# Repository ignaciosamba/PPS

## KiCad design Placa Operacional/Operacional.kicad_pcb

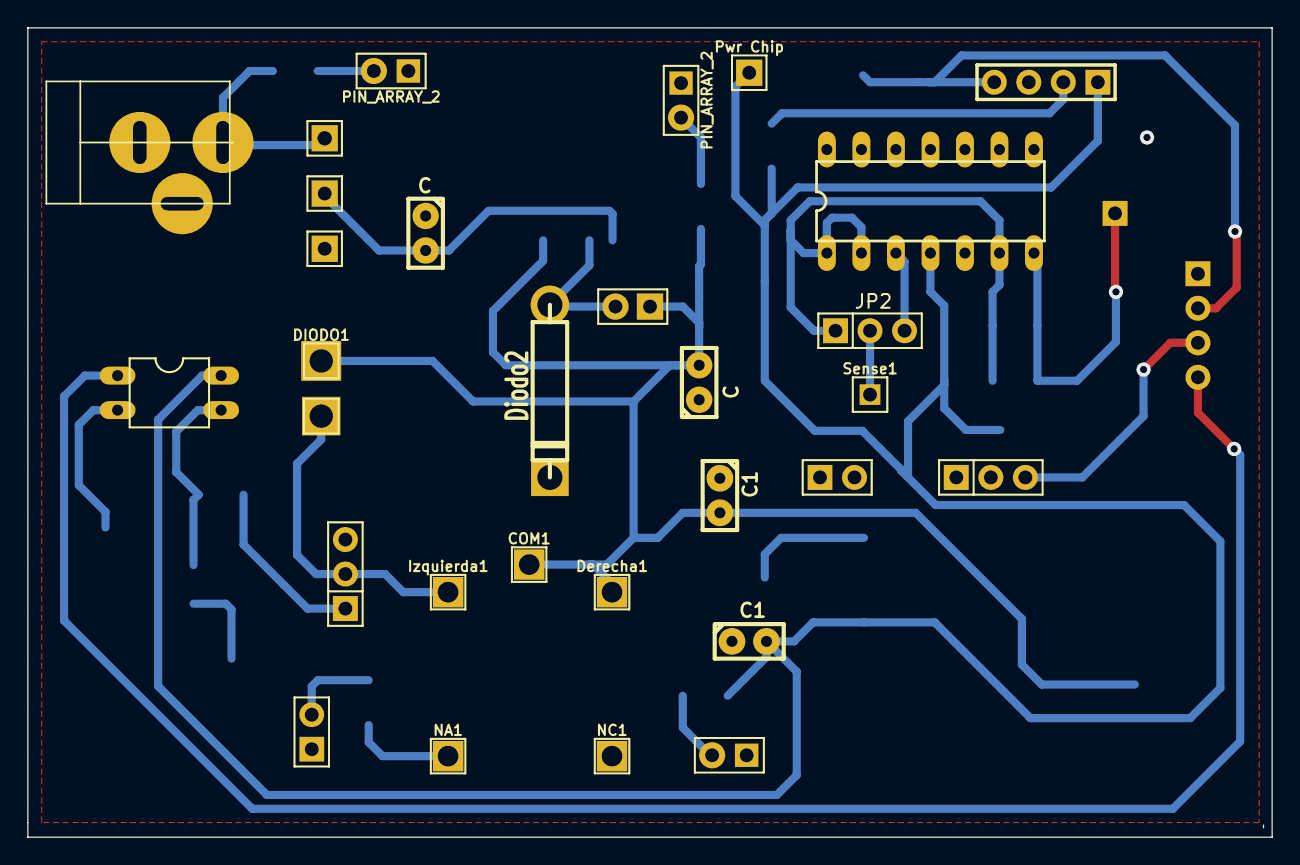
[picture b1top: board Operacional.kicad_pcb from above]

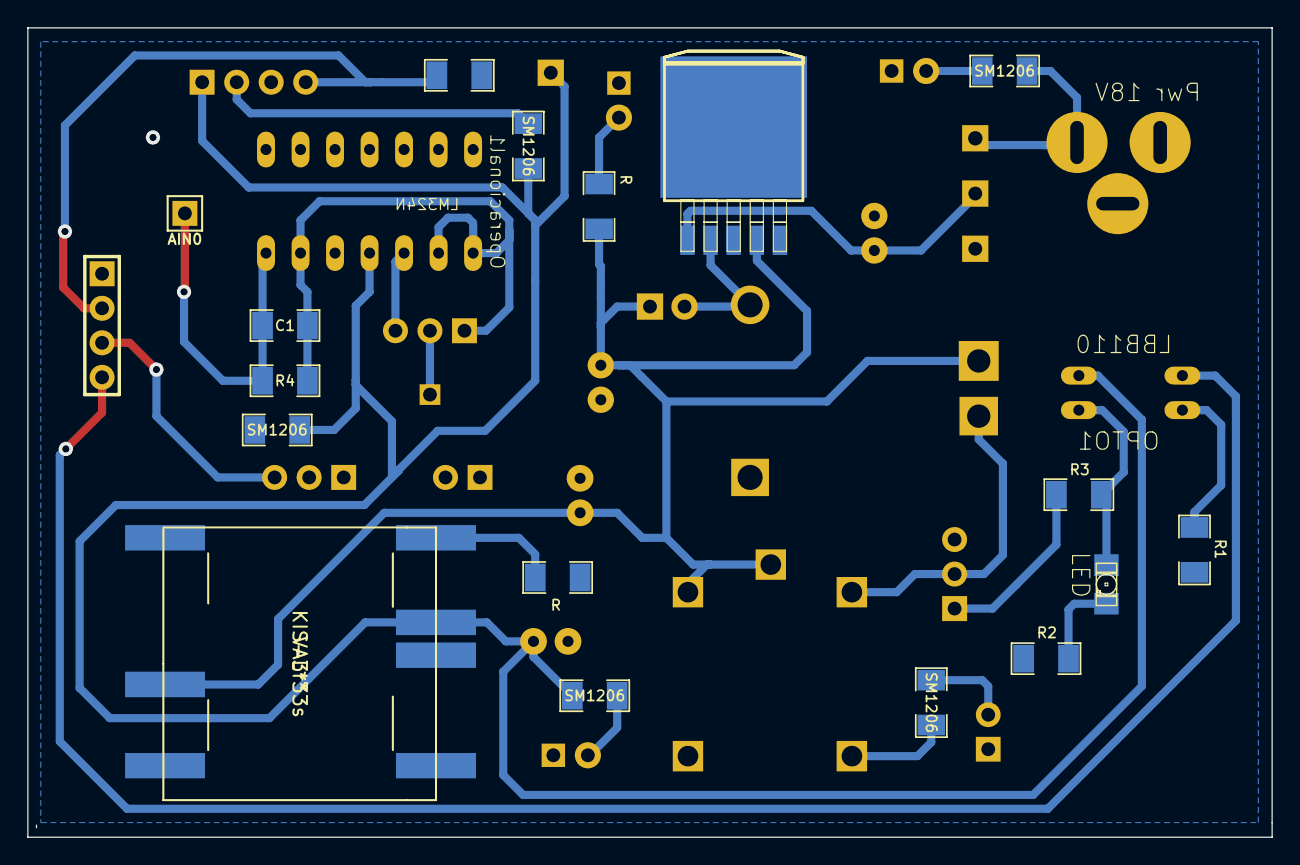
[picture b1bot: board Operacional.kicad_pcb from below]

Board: 2 copper layers, 91.6 x 59.6 mm, 32 parts (14 on the bottom side), 10 nets.

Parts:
AIN0: PIN_ARRAY_1
C: 100uF; C1
C1: 0.1uF; SM1206
C1#2, C1#3: C1
C#2: 1000uF; C1
COM1: PIN_ARRAY_1
DIODO1: PIN_ARRAY_1
Derecha1: PIN_ARRAY_1
Diodo2: D5
Izquierda1: PIN_ARRAY_1
JP2: PIN_ARRAY_3X1
KIS-3r33s: VAL**; KIS-3r33s
NA1: PIN_ARRAY_1
NC1: PIN_ARRAY_1
OPTO1: LBB110; optocoupler-2-DIL04
Operacional1: LM324N; op-amp-DIL14
PIN_ARRAY_2, PIN_ARRAY_2#2: Val**; PIN_ARRAY_2X1
Pwr Chip: PIN_ARRAY_1
R: 10K; SM1206
R1: 50; SM1206
R2: 1k; SM1206
R3, R4: 10k; SM1206
R#2: 1K; SM1206
SM1206, SM1206#2, SM1206#3, SM1206#4, SM1206#5: Val**; SM1206
Sense1: PIN_ARRAY_1

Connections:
GND: C.1, C1#2.1, C1#3.1, C#2.1, Diodo2.2, KIS-3r33s.2, KIS-3r33s.8, Operacional1.5, Operacional1.11, PIN_ARRAY_2.1, PIN_ARRAY_2#2.1, R.2, R1.2, R2.2, SM1206#5.2
unnamed: AIN0.1, C1.2, Operacional1.7, R4.2
unnamed: NA1.1, SM1206#3.1, SM1206#3.2
unnamed: C1.1, JP2.1, Operacional1.1, Operacional1.2, Operacional1.6, R4.1
unnamed: JP2.2, KIS-3r33s.5, R.1, Sense1.1
unnamed: JP2.3, Operacional1.3
unnamed: C.2, C1#2.2, C#2.2, COM1.1, DIODO1.1, Derecha1.1, Diodo2.1, KIS-3r33s.9, PIN_ARRAY_2.2, PIN_ARRAY_2#2.2, R#2.1, R#2.2, SM1206#2.1, SM1206#2.2
unnamed: OPTO1.2, R1.1
unnamed: OPTO1.3, R3.1
unnamed: C1#3.2, KIS-3r33s.4, OPTO1.4, Operacional1.4, Pwr Chip.1, SM1206.1, SM1206.2, SM1206#4.1, SM1206#4.2, SM1206#5.1

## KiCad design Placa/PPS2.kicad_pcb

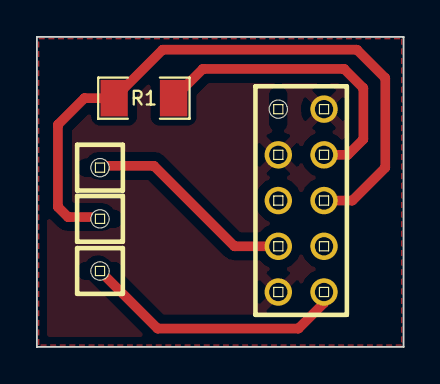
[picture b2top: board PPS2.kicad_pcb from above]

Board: 2 copper layers, 20.4 x 17.2 mm, 5 parts (0 on the bottom side), 5 nets.

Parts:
C2CLK1, C2DATOS1: PINHD-1X1; pinhead-1X01
JP1: PINHD-2X5; pinhead-2X05
PIN1: PINHD-1X1; pinhead-1X01
R1: 1K; SM1206

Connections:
GNDPWR: JP1.2, JP1.3, JP1.9
unnamed: JP1.4, R1.2
unnamed: C2CLK1.1, JP1.7
unnamed: C2DATOS1.1, JP1.6, R1.1
unnamed: JP1.10, PIN1.1

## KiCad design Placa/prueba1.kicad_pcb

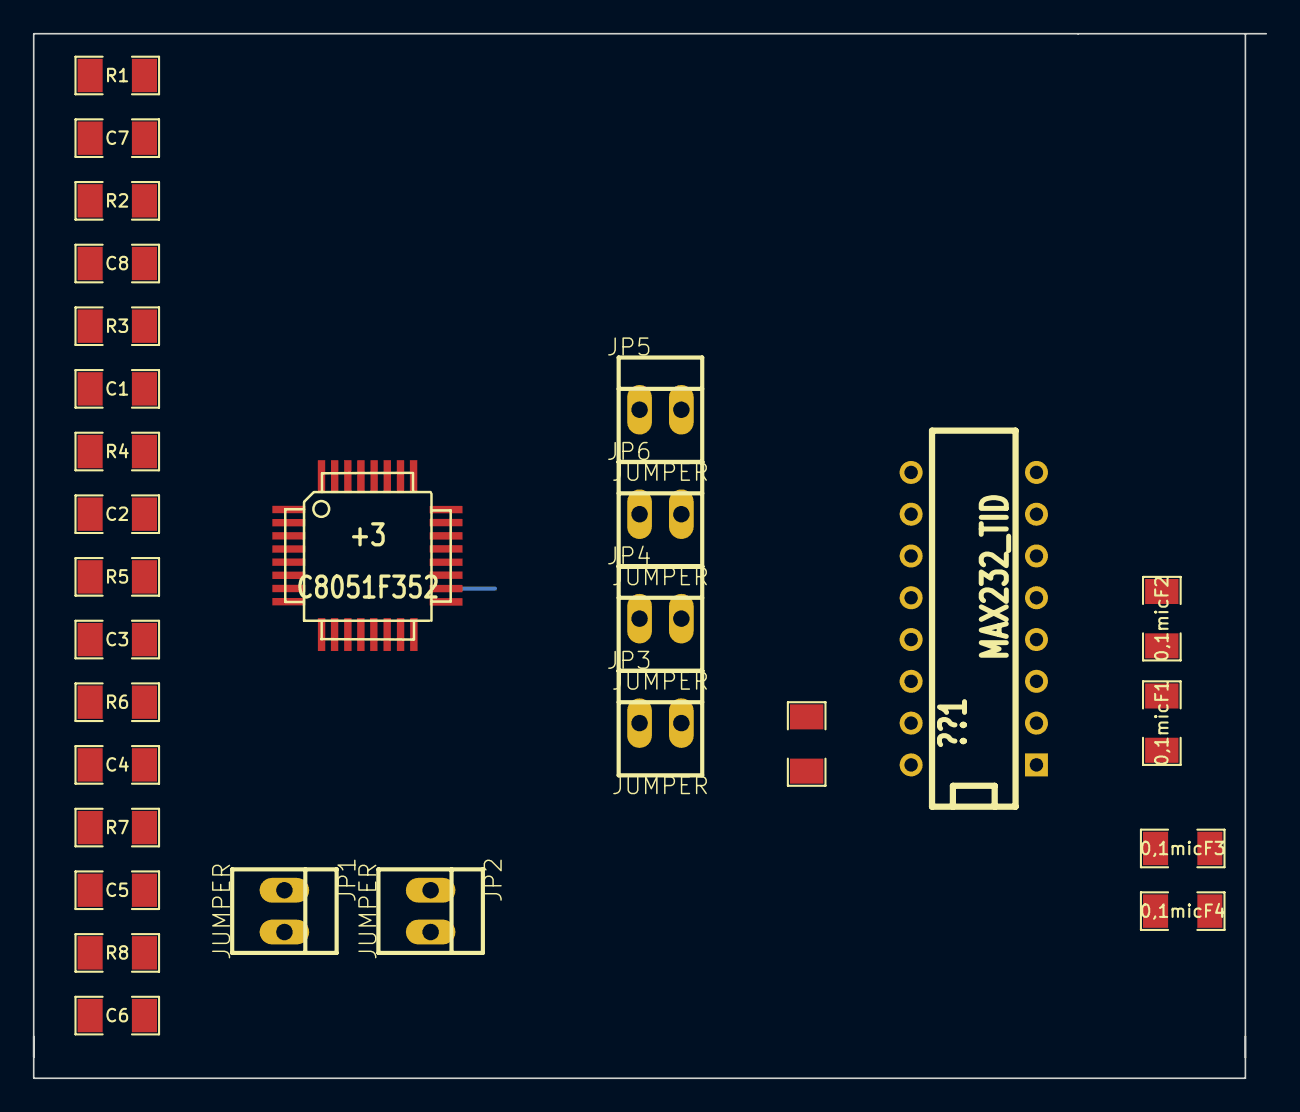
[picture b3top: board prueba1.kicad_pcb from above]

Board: 2 copper layers, 74.9 x 63.5 mm, 29 parts (0 on the bottom side), 36 nets.

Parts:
0,1micF1: C8; SM1206
0,1micF2: C9; SM1206
0,1micF3: C12; SM1206
0,1micF4: C10; SM1206
0,1micF5: C11; SM1206
+3: C8051F352; TQFP32
??1: MAX232_TID; DIP-16__300
C1, C2, C3, C4, C5, C6, C7, C8: 0,1micF; SM1206
JP1, JP2, JP3, JP4, JP5, JP6: JUMPER; PINHEAD1-2
R1, R2, R3, R4, R5, R6, R7, R8: 100ohm; SM1206

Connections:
DGND: C7.2, C8.2
GND: 0,1micF3.2, 0,1micF4.2, 0,1micF5.2, ??1.15
unnamed: 0,1micF1.1, ??1.1
unnamed: 0,1micF1.2, ??1.3
unnamed: +3.18, JP4.1
unnamed: +3.17, JP3.1
unnamed: +3.27, JP6.1
unnamed: +3.12, JP2.1
unnamed: +3.11, JP1.1
unnamed: 0,1micF2.1, ??1.4
unnamed: 0,1micF2.2, ??1.5
unnamed: +3.6, R6.2
unnamed: +3.1, R1.2
unnamed: +3.2, R2.2
unnamed: +3.3, R3.2
unnamed: +3.4, R4.2
unnamed: +3.5, R5.2
unnamed: 0,1micF5.1, ??1.16
unnamed: +3.7, R7.2
unnamed: +3.28, JP5.1
unnamed: ??1.9, JP6.2
unnamed: ??1.10, JP5.2
unnamed: ??1.12, JP4.2
unnamed: ??1.11, JP3.2
unnamed: 0,1micF3.1, ??1.6
unnamed: 0,1micF4.1, ??1.2
unnamed: +3.8, R8.2
unnamed: C8.1, R2.1
unnamed: C7.1, R1.1
unnamed: C1.1, R3.1
unnamed: C2.1, R4.1
unnamed: C3.1, R5.1
unnamed: C4.1, R6.1
unnamed: C5.1, R7.1
unnamed: C6.1, R8.1
VDD: +3.10, +3.21

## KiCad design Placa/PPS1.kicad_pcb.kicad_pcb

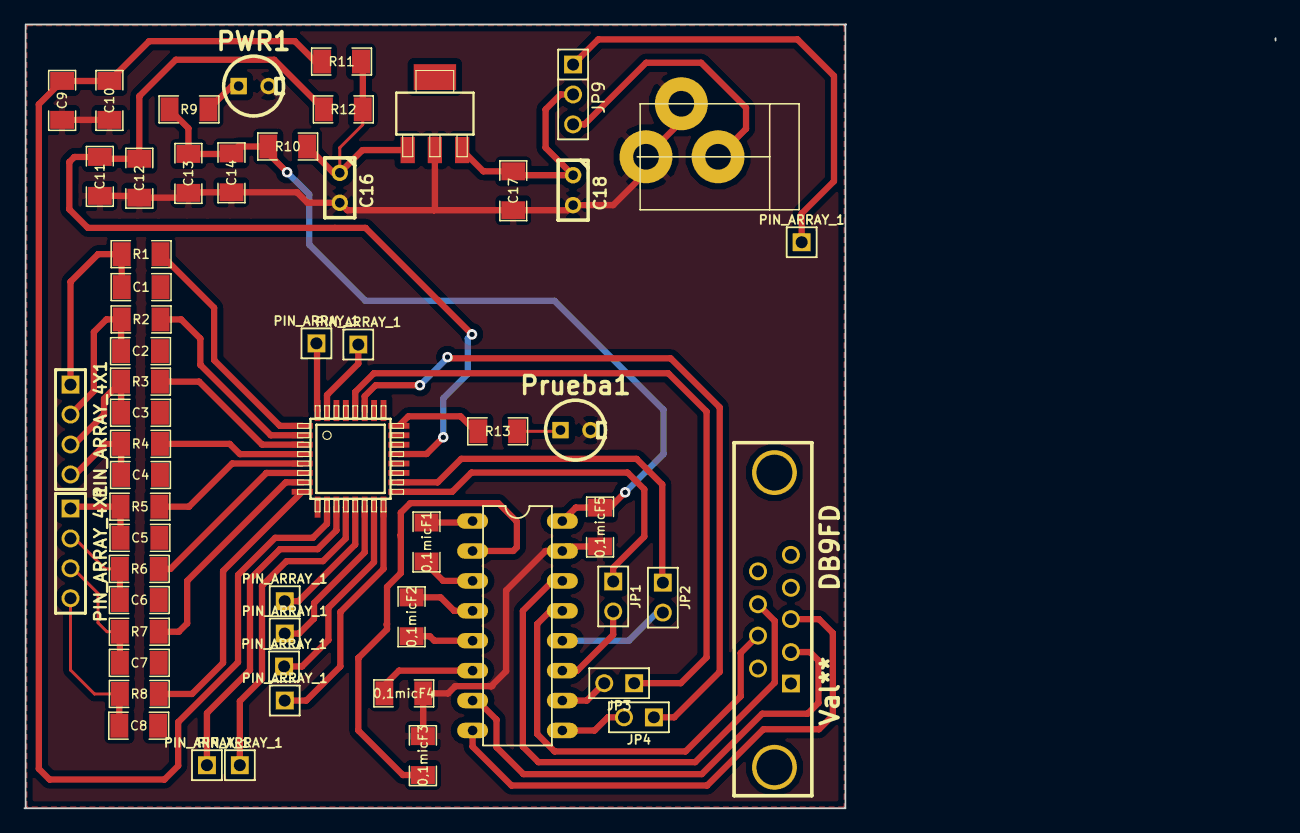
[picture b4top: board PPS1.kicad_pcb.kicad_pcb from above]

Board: 2 copper layers, 106.2 x 66.5 mm, 58 parts (0 on the bottom side), 43 nets.

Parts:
0,1micF1: C8; SM1206
0,1micF2: C9; SM1206
0,1micF3: C12; SM1206
0,1micF4: C10; SM1206
0,1micF5: C11; SM1206
+1: C8051F352; micro-silabs-LQFP32
C1, C2, C3, C4, C5, C6, C7, C8, C9, C10, C12, C13, C14: 0,1micF; SM1206
C11: 1micF; SM1206
C16: 15uF; C1
C17: C; SM1206
C18: 10uF; C1
DB9FD: Val**; DB9FD
J1: JACK_2P; POWER-IN-JACK-PMS
JP1, JP2, JP3, JP4: JUMPER; PIN_ARRAY_2X1
JP9: JUMPER3; PIN_ARRAY_3X1
PIN_ARRAY_1, PIN_ARRAY_1#2, PIN_ARRAY_1#3, PIN_ARRAY_1#4, PIN_ARRAY_1#5, PIN_ARRAY_1#6, PIN_ARRAY_1#7, PIN_ARRAY_1#8, PIN_ARRAY_1#9: Val**; PIN_ARRAY_1
PIN_ARRAY_4X1, PIN_ARRAY_4X1#2: Val**; PIN_ARRAY_4x1
PWR1: LED; LEDV
Prueba1: LED; LEDV
R1, R2, R3, R4, R5, R6, R7, R8: 100ohm; SM1206
R9, R13: 470; SM1206
R10, R11, R12: 2.0; SM1206
U1: MAX232_TID; max232ti_n-DIL16
U2: LM2937; lm2937-SOT223

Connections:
+3.3V: 0,1micF5.1, C13.1, C14.1, R9.1, R10.1, U1.16
DGND: C1.2, C2.2, C3.2, C4.2, C5.2, C6.2, C7.2, C8.2
GND: 0,1micF3.2, 0,1micF4.2, 0,1micF5.2, +1.22, C9.2, C10.2, C11.2, C12.2, C13.2, C14.2, C16.2, C17.2, C18.2, J1.1, J1.2, PWR1.2, Prueba1.2, U1.15, U2.2
unnamed: PWR1.1, R9.2
unnamed: Prueba1.1, R13.2
unnamed: JP4.2, U1.9
unnamed: JP3.2, U1.10
unnamed: JP2.2, U1.12
unnamed: +1.27, JP4.1
unnamed: C16.1, R10.2, R11.2, R12.2
unnamed: +1.12, PIN_ARRAY_1#3.1
unnamed: C17.1, C18.1, JP9.2, U2.3
unnamed: J1.3, JP9.3, PIN_ARRAY_1#4.1
unnamed: 0,1micF1.1, +1.13, PIN_ARRAY_1#6.1
unnamed: 0,1micF1.2, +1.18, JP2.1
unnamed: +1.16, PIN_ARRAY_1#9.1
unnamed: 0,1micF3.1, U1.2
unnamed: 0,1micF4.1, +1.14, PIN_ARRAY_1#7.1
unnamed: +1.15, DB9FD.3, PIN_ARRAY_1#8.1
unnamed: PIN_ARRAY_1.1, U1.14
unnamed: +1.11, DB9FD.2, PIN_ARRAY_1#2.1
unnamed: JP1.2, U1.11
unnamed: C5.1, R5.1
unnamed: +1.4, R4.2
unnamed: C4.1, PIN_ARRAY_4X1.4, R4.1
unnamed: +1.1, R1.2
unnamed: C1.1, PIN_ARRAY_4X1.1, R1.1
unnamed: +1.2, PIN_ARRAY_4X1#2.1, R2.2
unnamed: C2.1, R2.1
unnamed: +1.3, PIN_ARRAY_4X1.2, R3.2
unnamed: C3.1, R3.1
unnamed: PIN_ARRAY_4X1.3, U1.4
unnamed: +1.8, R8.2
unnamed: C8.1, PIN_ARRAY_4X1#2.4, R8.1
unnamed: +1.7, PIN_ARRAY_4X1#2.3, R7.2
unnamed: C7.1, R7.1
unnamed: +1.6, PIN_ARRAY_4X1#2.2, R6.2
unnamed: C6.1, R6.1
unnamed: +1.5, R5.2
unnamed: +1.17, JP1.1
unnamed: +1.28, JP3.1
unnamed: +1.10, C9.1, C10.1, R11.1
VDD: +1.21, C11.1, C12.1, R12.1

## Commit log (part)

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2015-04-20 :space_invader: Added .gitattributes & .gitignore files
2015-04-20 a ver que pasa
2015-04-20 Revert "Revert "a ver que pasa""
    This reverts commit ce52e4edb60050e8a4856e37b82e109fdb21671b.
2015-04-21 ultimo commit
2015-04-21 Comentario
    Agregue comentarios en la parte del Swapeo.
2015-04-21 mi archivo
2015-04-24 puse un par de cosas en los archivos
    y cree el proyecto..
2015-04-27 puse un par de cosas mas a los fuentes
    silabs me lo compila pero tira warnings.. tengo que empezar a tirar
    magia...
2015-04-28 haciendo el test
    la idea es que test global corra todos los tests.. tengo que terminarlo
    pero me tengo que alzar al ogt. se vemo
2015-05-04 HAY
    bastantes quilombos internos.. pero se podria decir que va tomando
    forma. estoy cambiando el archivo interfaz.c para que tenga una forma de
    tomar los pines que siga el sentido comun.. pero se esta complicando..
    hay que empezar a hacer tests que verifiquen que anden las opciones de
    configuracion.. para el proximo commit deberian estar los tests hechos
2015-05-05 Commit Prueba Archivos Placa
2015-05-05 nuevo log
    lalala
2015-05-07 Cambio a convertir
    Cambio el dato_a_convertir a puntero
2015-05-07 Envio dato sin puntero.
2015-05-07 nada
2015-05-07 esta incompletp
    esta la idea de hacer el array con la informacion de los pines single
    ended pero no esta implementado porque estuvimos 40 horas discutiendo de
    a donde y como hacer el array
2015-05-08 SIN ERRORES 2
    NO FUNCIONA NADA!
2015-05-08 git ignore 2
2015-05-11 prueba git ignore
    prueba para ver si desde ahora me deja de trackear los archivos que no
    quiero que esten en el repo
2015-05-11 otro ignore mas
2015-05-11 commit para ver los cambios
    este comit tiene los archivos fuente del commit "ADC andando con el
    MULTIPLEXOR". quiero comparar ese con el ultimo commit.. osea "no anda
    nada" y ver que tocamos para que se rompa tanto todo
2015-05-11 Funcionando la Interfaz para Single Ended.
2015-05-11 Anda como la SILVANA
2015-05-11 Otro comit!
2015-05-12 sdfd
2015-05-12 se acabo la joda
    el compilador me dice que el codigo es muy grande para la version de
    prueba asi que comiteo esto y voy a buscar compiladores open source. una
    verga
2015-05-14 Ya funcionando bien.
2015-05-14 Memoria 3
    hice algunos tests para verificar que las funciones de memoria que
    sacamos de las notas de aplicacion andan como parece que andan.
2015-05-14 Compila test, errores
2015-05-15 para el orto
    anda todo bastante para la teta, y encima cuando se decide por compilar,
    me tira el error de address space overflow que me dejo de cara mal
2015-05-18 compilan los tests
    ahi saque andando los tests.. no tengo ni puta idea de porque andaron..
    descomente un pedazo de codigo y volvio a andar a pleno ni idea pq la
    verdad.. me esta preocupando el tema del tamaño del codigo porque ya va
    por 4300 bytes mas o menos y tenemos 8K como maximo y nos falta
    bastante.. o achicamos codigo o trabajamos en assembler. ponele
2015-05-18 nuevo framework de test.. aver que pasa
2015-05-19 gitignore nuevo
2015-05-19 guarde
2015-05-19 nada
    todo esta igual
2015-05-20 hice mas cagada aun.. espero que todo esto valga la pena bolos
2015-05-22 compila pero no puedo probarlo
    acomode todos los archivos a los cambios que hice y con todas las
    funciones logicas testeadas.. como el tragaleche de sambataro esta
    probando cosas con la placa no puedo probarlo todavia. los archivos
    comunicacion, memoria e impresiones no se usan mas.. interfaz_viejo no
    se usa.. lo deje ahi por que estan las funciones viejas por las dudas
2015-05-22 cambie un par de cosas pero mepa que al micro se le arma quilombo con los punteros
2015-05-26 comandos y log
2015-05-29 committ
    cambis de antes de irme el martes pasado y cambios que hice ayer.
2015-06-04 FUNCIONAAA!!!!
    El contador, funciona, la concha de tu madre all boys!
2015-06-05 TIMER 2 Y TIMER 3
    sume al proyecto las funciones para configurar timer2 y 3.. pero creo
    que timer 3 nos lo vamos a tener que meter por el orto poruqe la fuente
    externa que elige es la misma que la de timer 2 asi que basicamente van
    a contar lo mismo.. por lo que no sirve.. lo que pienso es usar el PCA y
    dejar al timer 3 como un contador interno para alguna otra cosa que haga
    falta. el archivo contador.c en timer tiene todo implementado para hacer
2015-06-12 cambie algunas cosas para el PCA
    pero el PCA sigue sin andar.. algun dia andara. ahora sale flash
2015-06-12 flash
    hice varias cosas de la flash, estan los comandos para cargarla,
    modificarla, etc.. soy un pelotudo porque tendria que haber hecho un
    commit cuando tenia hecha bien la escritura porque ahora no me escribe y
    no se porque
2015-06-15 FLASH ANDANDO
    en teroria estaria andando.. esta escribiendo los datos en la direccion
    0x01F0 que esta dentro de la primera pagina de la flash, que es de
    datos. no hay nada en esa ultima franja asi que estamos escribiendo en
    la nada misma lo cual no deberia traer problemas.. pero igual estamos
    usando como zona temporal la 0x1A00 que en cualquier momento empieza a
    ser parte de codigo asi que no creo que dure mucho. alta fe
2015-06-18 arreglado el git ignore
2015-06-19 AHI ARREGLE
    bueno no tira mas error cuando pones solo enter. ahora hago este commit
    para ya cambiar el adc para siempre muajaja
2015-06-19 se estaba subiendo el hex asi que lo agregue al ignore
2015-06-25 ahi anda mejor
    va queriendo, ya no confunde las patas.. pero falta ponerle un poco de
    deteccion de errores al SSE nuevo y habilitar el seteo de patas
    diferenciales con SDI
2015-06-25 un bajon
    en algo la esta cagando la funcion cambiar_pin() porque sin esa funcion
    las patas miden excelente y con esa funcion miden para el traste.. ni
    idea que podra ser pero anda muy para atras
2015-06-29 volvieron los testss
    hice los tests de hardware haciendo un test completo entero de pecho..
    que se llama test_conversor
2015-07-01 mas cosas
    subi un par de cosas.. estoy tratando de que se pueda volver al menu
    desde la impresion de las conversiones.. pero esta duro.. hice un par de
    tablas en excel y actualice el log. me voy al orto
2015-07-10 ahi andan los tests basicos
    separe el de blink led con el del resto porque es un test muy basico..
    es el primero que se tiene que probar y deberia estar separado
2015-07-22 mas refactory
    cambie los headers de los tests. pero por alguna razon lo probe y no
    imprime nada en el realterm
2015-07-22 bug fix
    habia borrado sin querer una linea de codigo que no dejaba que arranque
    la obtencion de la entrada. ahi la volvi a poner y volvio a andar
2015-07-22 Parar ADC con UART
2015-07-23 cambio y error
    quise hacer un cambio re estupido en la interfaz para que imprima una
    giladad cuando pongo ST y me di cuenta que de pecho dejo de andar la
    configuracion de diferencial.. algo habre hecho
2015-07-31 agregue funciones
    agregue dos funciones para que estando en la interfaz de usuario se
    pueda pedir un dato de conversion inmediato.. onda lo mismo que con los
    timers.. adquisicion por demanda.. falta probbarlos
2015-08-21 arreglando bugs
    hay un bug en el modo diferencial, lo puedo setear pero no arranca la
    conversion. lo veo el lunes
2015-08-25 saque por completo la flash
    como no la usamos porque es una porqueria las cosas que hace teniendo
    tan poca memoria, la sacamos al carajo y vamos a buscar otra manera de
    guardar la configuracion.. estoy probando el test de la interfaz pero no
    sale bien
2015-09-02 va queriendo
    hay que probarlo con la placa de parlanti que la tienen los otros
    culiados asi que no puedo probar nada hasta no tenerla
2015-09-09 el timer anda, pero mal...
    voy a tratar de hacerlo con el timer en modo 8 bit en vez de 16
2015-09-10 ahi anda y se queda estable, pero...
    hay una forma mucho mas facil y rapida de hacer anda todo y es usando el
    puto modulo de pwm que tiene la silicon labs que me acabo de enterar que
    tiene... asi q cambio todo
2015-09-10 ahi anda mortal
    ahora lo que hay que ahcer es calibrar los tiempos de ciclo de trabajo
    para que hagan andar al driver.
2015-09-14 ahi esta el modulo de pwm integrado al embebido
    deberia andar, no lo pobe aun
2015-09-17 ahi parece que andaria
    hay un problema con las interrupciones del PCA.. si las deshabilito anda
    todo.. queda probar si anda bien el PCA, que no creo.. pero ya te juro q
    todo es posible
2015-09-17 funcion de control
    hice una funcion de control para ver si se mantienen mejor las RPM.. no
    la pude probar todavia porque me sacaron la fuente.. mañana la pruebo
2015-09-21 volvio a andar el pwm
    le saco las interrupciones porque anda sin interrupciones no tiene
    sentido que no tenga las interrupciones pero si le pongo las
    interrupciones anda para el orto. asi que le saco las interrupciones
2015-09-22 con la division de mV anterior
2015-09-22 arreglando bugs y haciendo mas tests
    arregle el bug para SDI, GSE y GDI, y agregue tests para SSE y la
    interfaz
2015-09-23 Primera aproximacion de SAMBA a latex!
    Descripcion de HARDWARE
2015-09-25 segundo release
    ya vendriamos teniendo todo listo.. termine todos los tests y verifique
    que ande todo bien con la placa y todo.. asi que ya estaria lista la
    parte de todo lo que es la concentradora y las funciones para el motor.
    nomas esta el detalle del control de velocidad que hay que calibrarlo
    para que no oscile tanto. pero el resto esta. desde aca saco un branch
    que es para que ande todo con el modulo de comunicacion de gaston y juan
2015-09-25 ahi anda la conversion diferencial pero no los get
2015-09-28 anda todo sin control de rpm
2015-09-29 anda medio raro
    me parece que la baja de presicion que le hice de pasar a medir cada
    500ms a 100ms hace que se rompa todo.. voy a probar una cosa pasando a
    medir rps en vez de rpm cualquier cosa multiplico por sesenta para
    imprimir
2015-09-29 anda mejor ahi
    le cambie para que el control sea basado en las vueltas cada 100
    milisegundos y no en rpm como hacia antes tab brutamente.. pero igual
    sigue medio inestable.. hay que ver que pasa
2015-10-05 agregue funciones para los modos de bajo consumo
    cada funcion tiene retornos de tipo acknowledge que se envian por UART.
    800 = bajo consumo habilitado
    801 = bajo consumo inhabilitado
2015-10-16 agregue los modos de bajo consumo
2015-10-23 mas documentaciones
2015-10-29 arreglando y comprendiendo el motor
2015-10-30 documentando
2015-11-02 mas cosasss
2015-11-03 mas cambios
2015-11-06 ya casi el informee culiaa
2015-11-06 avances de hardware
2016-03-10 volviendo de las vacaciones. empece el informe de las 200 horas y agregue un par de imagenes. no cambie nada del codigo pero lo compile una vez mas para ver que onda y parece que anda todo bien. ahor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
2016-03-10 me olvide de hacer stage files en el commit anterior
2016-04-01 nuevo proyecto creado con uvision3 porque no consegui el crack para el 4 y este anda joya
2016-04-07 Requerimientos!
2016-05-04 hay un monton de cosas nuevas.. pero la razon por la cual commiteo es por los test cases en excel nuevos.. para que los veas.. espero que esto no rompa absolutamente todo
2016-05-06 Agrego Archivos
    Informes y Nuevos Objetivos.
2016-05-13 CAMBIOS EN AGUNAS COSAS
2016-06-06 no anda el timestamp. voy a probar otra manera pero commiteo para guardar por las dudas
2016-06-10 Agregados los Objetivos.
2016-06-14 actualizacion de diagramas en el enterprise. agregue tambien unos txt con los requerimientos del sistema
2016-06-16 agregue diagrama de bloques de sistema fisico para el sistema de procesado y guardado
2016-09-18 refactorizado de los comentarios y cosas nuevas
2016-09-21 mas diagramas
2016-10-03 MAIS DIAGRAMAS MRD EZ GG
2016-10-07 diagrama de actividad para analizar buffer
2016-10-11 diagrama de actividad de la interfaz
2016-10-22 no se que bosta hice ni me acuerdo
2016-11-21 diagrama cambiar pin primera iteracion
2016-12-06 diagrama de bloques del sistema de gestion y diagrama de interaccion entre el sistema de gestion y la plataforma de instrumentacion
2017-03-03 me falto el vertical
2017-09-07 funciones sensor
2017-09-15 medir hertz
